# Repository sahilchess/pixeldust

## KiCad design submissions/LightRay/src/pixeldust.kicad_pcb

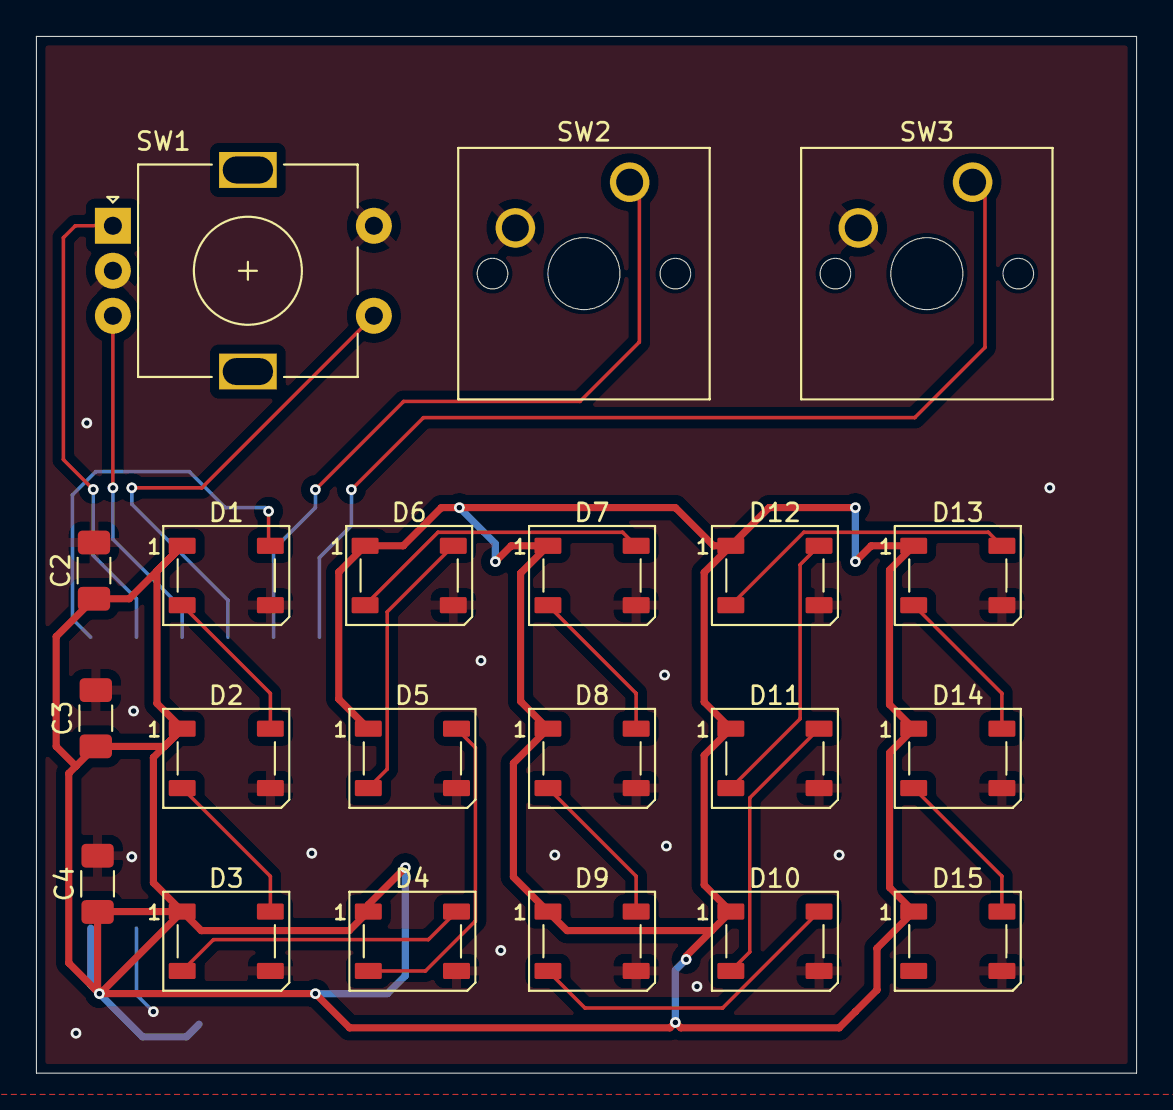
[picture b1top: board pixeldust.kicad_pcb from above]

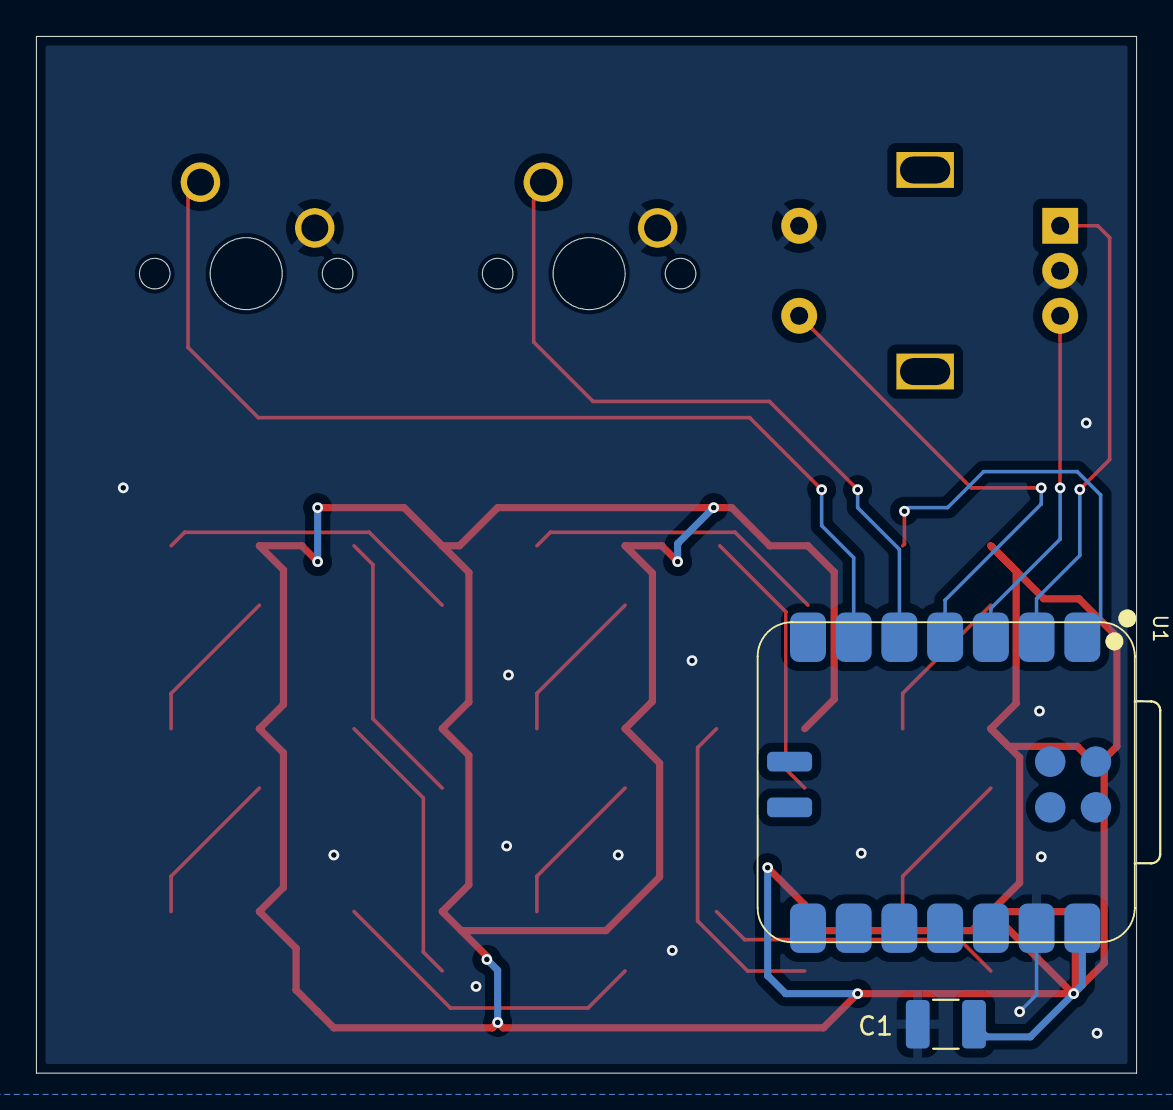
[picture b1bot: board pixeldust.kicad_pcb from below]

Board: 2 copper layers, 61.1 x 57.6 mm, 23 parts (2 on the bottom side), 22 nets.

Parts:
C1: 100uF; C_1210_3225Metric_Pad1.33x2.70mm_HandSolder
C2, C3, C4: 4.7nF; C_1206_3216Metric_Pad1.33x1.80mm_HandSolder
D1, D2, D3, D4, D5, D6, D7, D8, D9, D10, D11, D12, D13, D14, D15: WS2812B; LED_WS2812B_PLCC4_5.0x5.0mm_P3.2mm
SW1: RotaryEncoder_Switch; RotaryEncoder_Alps_EC11E-Switch_Vertical_H20mm
SW2, SW3: SW_Push; SW_Cherry_MX_1.00u_PCB
U1: XIAO-RP2040-SMD

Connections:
+5V: C1.1, C2.1, C3.1, C4.1, D1.1 (VDD), D2.1 (VDD), D3.1 (VDD), D4.1 (VDD), D5.1 (VDD), D6.1 (VDD), D7.1 (VDD), D8.1 (VDD), D9.1 (VDD), D10.1 (VDD), D11.1 (VDD), D12.1 (VDD), D13.1 (VDD), D14.1 (VDD), D15.1 (VDD), U1.14 (5V)
GND: C1.2, C2.2, C3.2, C4.2, D1.3 (VSS), D2.3 (VSS), D3.3 (VSS), D4.3 (VSS), D5.3 (VSS), D6.3 (VSS), D7.3 (VSS), D8.3 (VSS), D9.3 (VSS), D10.3 (VSS), D11.3 (VSS), D12.3 (VSS), D13.3 (VSS), D14.3 (VSS), D15.3 (VSS), SW1.C, SW1.S2, SW2.2, SW3.2, U1.13 (GND)
LED: D1.4 (DIN), U1.1 (GPIO26_A0_D0)
unnamed: D1.2 (DOUT), D2.4 (DIN)
unnamed: D2.2 (DOUT), D3.4 (DIN)
unnamed: D3.2 (DOUT), D4.4 (DIN)
unnamed: D4.2 (DOUT), D5.4 (DIN)
unnamed: D5.2 (DOUT), D6.4 (DIN)
unnamed: D6.2 (DOUT), D7.4 (DIN)
unnamed: D7.2 (DOUT), D8.4 (DIN)
unnamed: D8.2 (DOUT), D9.4 (DIN)
unnamed: D9.2 (DOUT), D10.4 (DIN)
unnamed: D10.2 (DOUT), D11.4 (DIN)
unnamed: D11.2 (DOUT), D12.4 (DIN)
unnamed: D12.2 (DOUT), D13.4 (DIN)
unnamed: D13.2 (DOUT), D14.4 (DIN)
unnamed: D14.2 (DOUT), D15.4 (DIN)
ROTA: SW1.A, U1.2 (GPIO27_A1_D1)
ROTB: SW1.B, U1.3 (GPIO28_A2_D2)
ROTSW: SW1.S1, U1.4 (GPIO29_A3_D3)
SW1: SW2.1, U1.5 (GPIO6_D4_SDA)
SW2: SW3.1, U1.6 (GPIO7_D5_SCL)
